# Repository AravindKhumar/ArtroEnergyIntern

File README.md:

# ArtroEnergyIntern
Contains the codes that were created to log data from Growatt inverter using RPi and NodeMCU and put the data in to the cloud for analytics

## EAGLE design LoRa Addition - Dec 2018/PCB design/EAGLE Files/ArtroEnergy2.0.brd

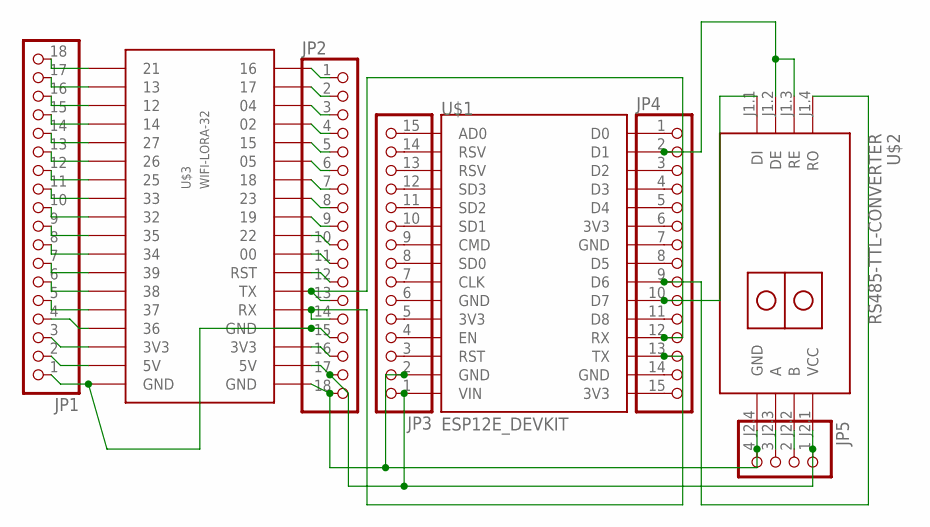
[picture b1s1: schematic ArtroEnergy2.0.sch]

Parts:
JP1, JP2: PINHD-1X18; 1X18
JP3, JP4: PINHD-1X15; 1X15
JP5: PINHD-1X4; 1X04
U$1: ESP12E_DEVKIT
U$2: RS485-TTL-CONVERTER
U$3: WIFI-LORA-32; 2.54MM_2X18

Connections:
3V3@1: JP2.16, U$3.P$3 (3V3)
3V3@2: JP1.3, U$3.P$34 (3V3)
5V@1: JP2.17, JP3.1, JP5.1, U$1.VIN, U$2.J2.1 (VCC), U$3.P$2 (5V)
5V@2: JP1.2, U$3.P$35 (5V)
D0: JP4.10, U$1.D7, U$2.J1.1 (DI)
DE_RE: JP4.2, U$1.D1, U$2.J1.2 (DE), U$2.J1.3 (RE)
GND@1: JP2.18, JP3.2, JP5.4, U$1.GND@1 (GND), U$2.J2.4 (GND), U$3.P$1 (GND)
GND@2: JP1.1, JP2.15, U$3.P$4 (GND), U$3.P$36 (GND)
unnamed: JP1.18, U$3.P$19 (21)
unnamed: JP1.17, U$3.P$20 (13)
unnamed: JP1.16, U$3.P$21 (12)
unnamed: JP1.15, U$3.P$22 (14)
unnamed: JP1.14, U$3.P$23 (27)
unnamed: JP1.13, U$3.P$24 (26)
unnamed: JP1.12, U$3.P$25 (25)
unnamed: JP1.11, U$3.P$26 (33)
unnamed: JP1.10, U$3.P$27 (32)
unnamed: JP1.9, U$3.P$28 (35)
unnamed: JP1.8, U$3.P$29 (34)
unnamed: JP1.7, U$3.P$30 (39)
unnamed: JP1.6, U$3.P$31 (38)
unnamed: JP1.5, U$3.P$32 (37)
unnamed: JP1.4, U$3.P$33 (36)
unnamed: JP2.1, U$3.P$18 (16)
unnamed: JP2.2, U$3.P$17 (17)
unnamed: JP2.3, U$3.P$16 (04)
unnamed: JP2.4, U$3.P$15 (02)
unnamed: JP2.5, U$3.P$14 (15)
unnamed: JP2.6, U$3.P$13 (05)
unnamed: JP2.7, U$3.P$12 (18)
unnamed: JP2.8, U$3.P$11 (23)
unnamed: JP2.9, U$3.P$10 (19)
unnamed: JP2.10, U$3.P$9 (22)
unnamed: JP2.11, U$3.P$8 (00)
unnamed: JP2.12, U$3.P$7 (RST)
unnamed: JP3.3, U$1.RST
unnamed: JP3.4, U$1.EN
unnamed: JP3.5, U$1.3V3@0 (3V3)
unnamed: JP3.6, U$1.GND@0 (GND)
unnamed: JP3.7, U$1.CLK
unnamed: JP3.8, U$1.SD0
unnamed: JP3.9, U$1.CMD
unnamed: JP3.10, U$1.SD1
unnamed: JP3.11, U$1.SD2
unnamed: JP3.12, U$1.SD3
unnamed: JP3.13, U$1.RSV@1 (RSV)
unnamed: JP3.14, U$1.RSV@0 (RSV)
unnamed: JP3.15, U$1.AD0
unnamed: JP4.1, U$1.D0
unnamed: JP4.3, U$1.D2
unnamed: JP4.4, U$1.D3
unnamed: JP4.5, U$1.D4
unnamed: JP4.6, U$1.3V3@1 (3V3)
unnamed: JP4.7, U$1.GND@2 (GND)
unnamed: JP4.8, U$1.D5
unnamed: JP4.11, U$1.D8
unnamed: JP4.14, U$1.GND@3 (GND)
unnamed: JP4.15, U$1.3V3@2 (3V3)
unnamed: JP5.2, U$2.J2.2 (B)
unnamed: JP5.3, U$2.J2.3 (A)
RO: JP4.9, U$1.D6, U$2.J1.4 (RO)
RX-TX: JP2.14, JP4.13, U$1.TX, U$3.P$5 (RX)
TX-RX: JP2.13, JP4.12, U$1.RX, U$3.P$6 (TX)

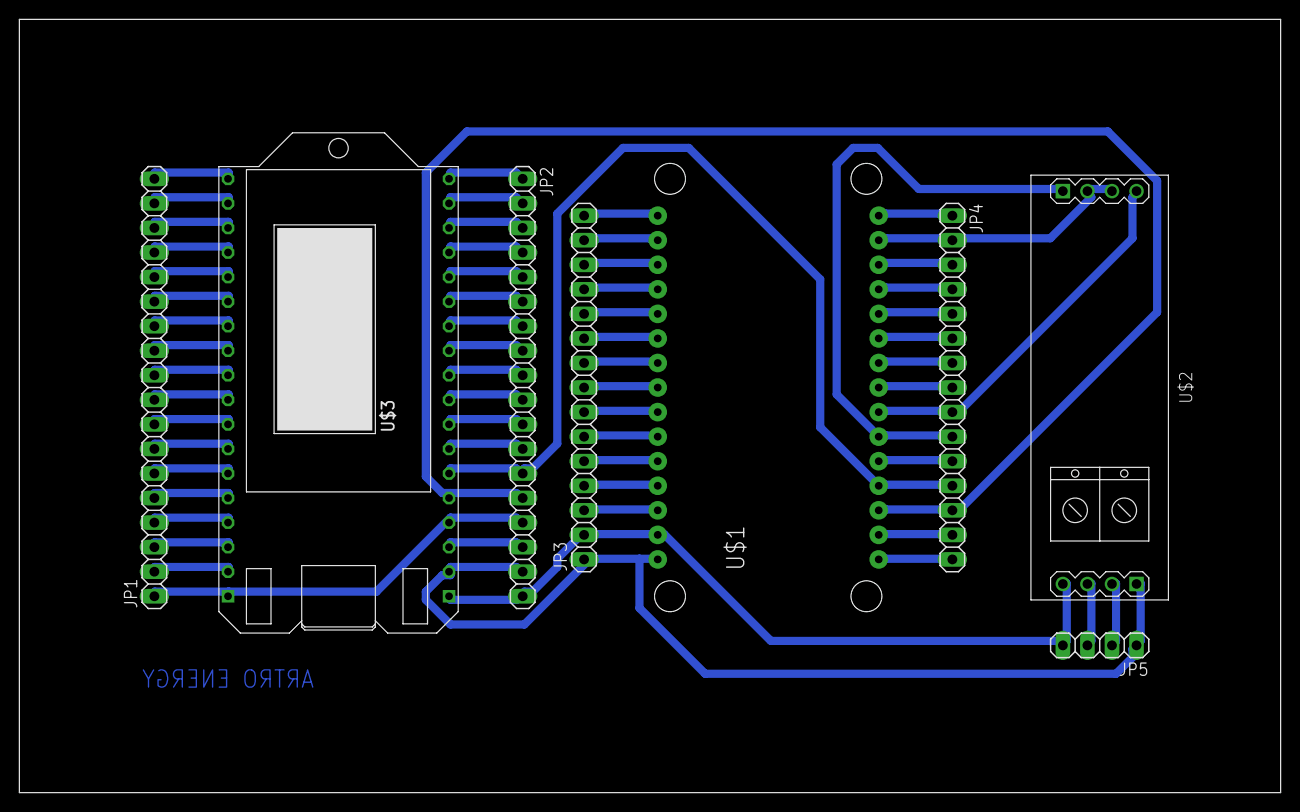
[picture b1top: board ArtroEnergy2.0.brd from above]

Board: 2 copper layers, 130.5 x 80.0 mm, 8 parts (0 on the bottom side), 63 nets.

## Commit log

2021-09-01 Created TEADME.md

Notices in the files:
parts and their libraries:
diy-modules: Released under the Creative Commons Attribution 4.0 International License: http://creativecommons.org/licenses/by/4.0
